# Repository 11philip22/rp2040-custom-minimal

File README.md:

# RP2040 Minimal Project for KiCad

**RP2040 Minimal** is a circuit design based on Raspberry Pi's **RP2040** microcontroller, provided as a **KiCad** project. This repository contains the `RP2040_minimal-edit_V3` revision by [Gerald](https://community.element14.com/members/geralds), which retains the original PCB outline and GPIO connectors while updating the layout, component sizes, and USB interface.

| Front | Back |
| :---: | :---: |
|  |  |

## Design Overview

1. Uses a **USB Type-C** connector in place of the original Micro USB connector.
2. Uses `0603` components in place of `0402` parts for easier assembly.
3. Improves the PCB layout while retaining the original board outline and **GPIO connectors**.
4. Includes improved **ESD protection** at the USB interface.
5. Includes project-local **symbols**, **footprints**, and **3D models** for editing the design in KiCad.

## Notes

- Open [`minimal-edit_V3.kicad_pro`](./minimal-edit_V3.kicad_pro) in **KiCad** to work with the schematic and PCB layout.
- Keep the bundled library directories alongside the project; the symbol and footprint tables use project-relative paths.

## Technical Documentation

The repository includes the following design files and previews:

- [KiCad Schematic](./minimal-edit_V3.kicad_sch)
- [KiCad PCB Layout](./minimal-edit_V3.kicad_pcb)
- [Schematic Preview](./images/RP2040-minimal-Rev3_sch.png)

| Front PCB Layout | Back PCB Layout |
| :---: | :---: |
|  |  |

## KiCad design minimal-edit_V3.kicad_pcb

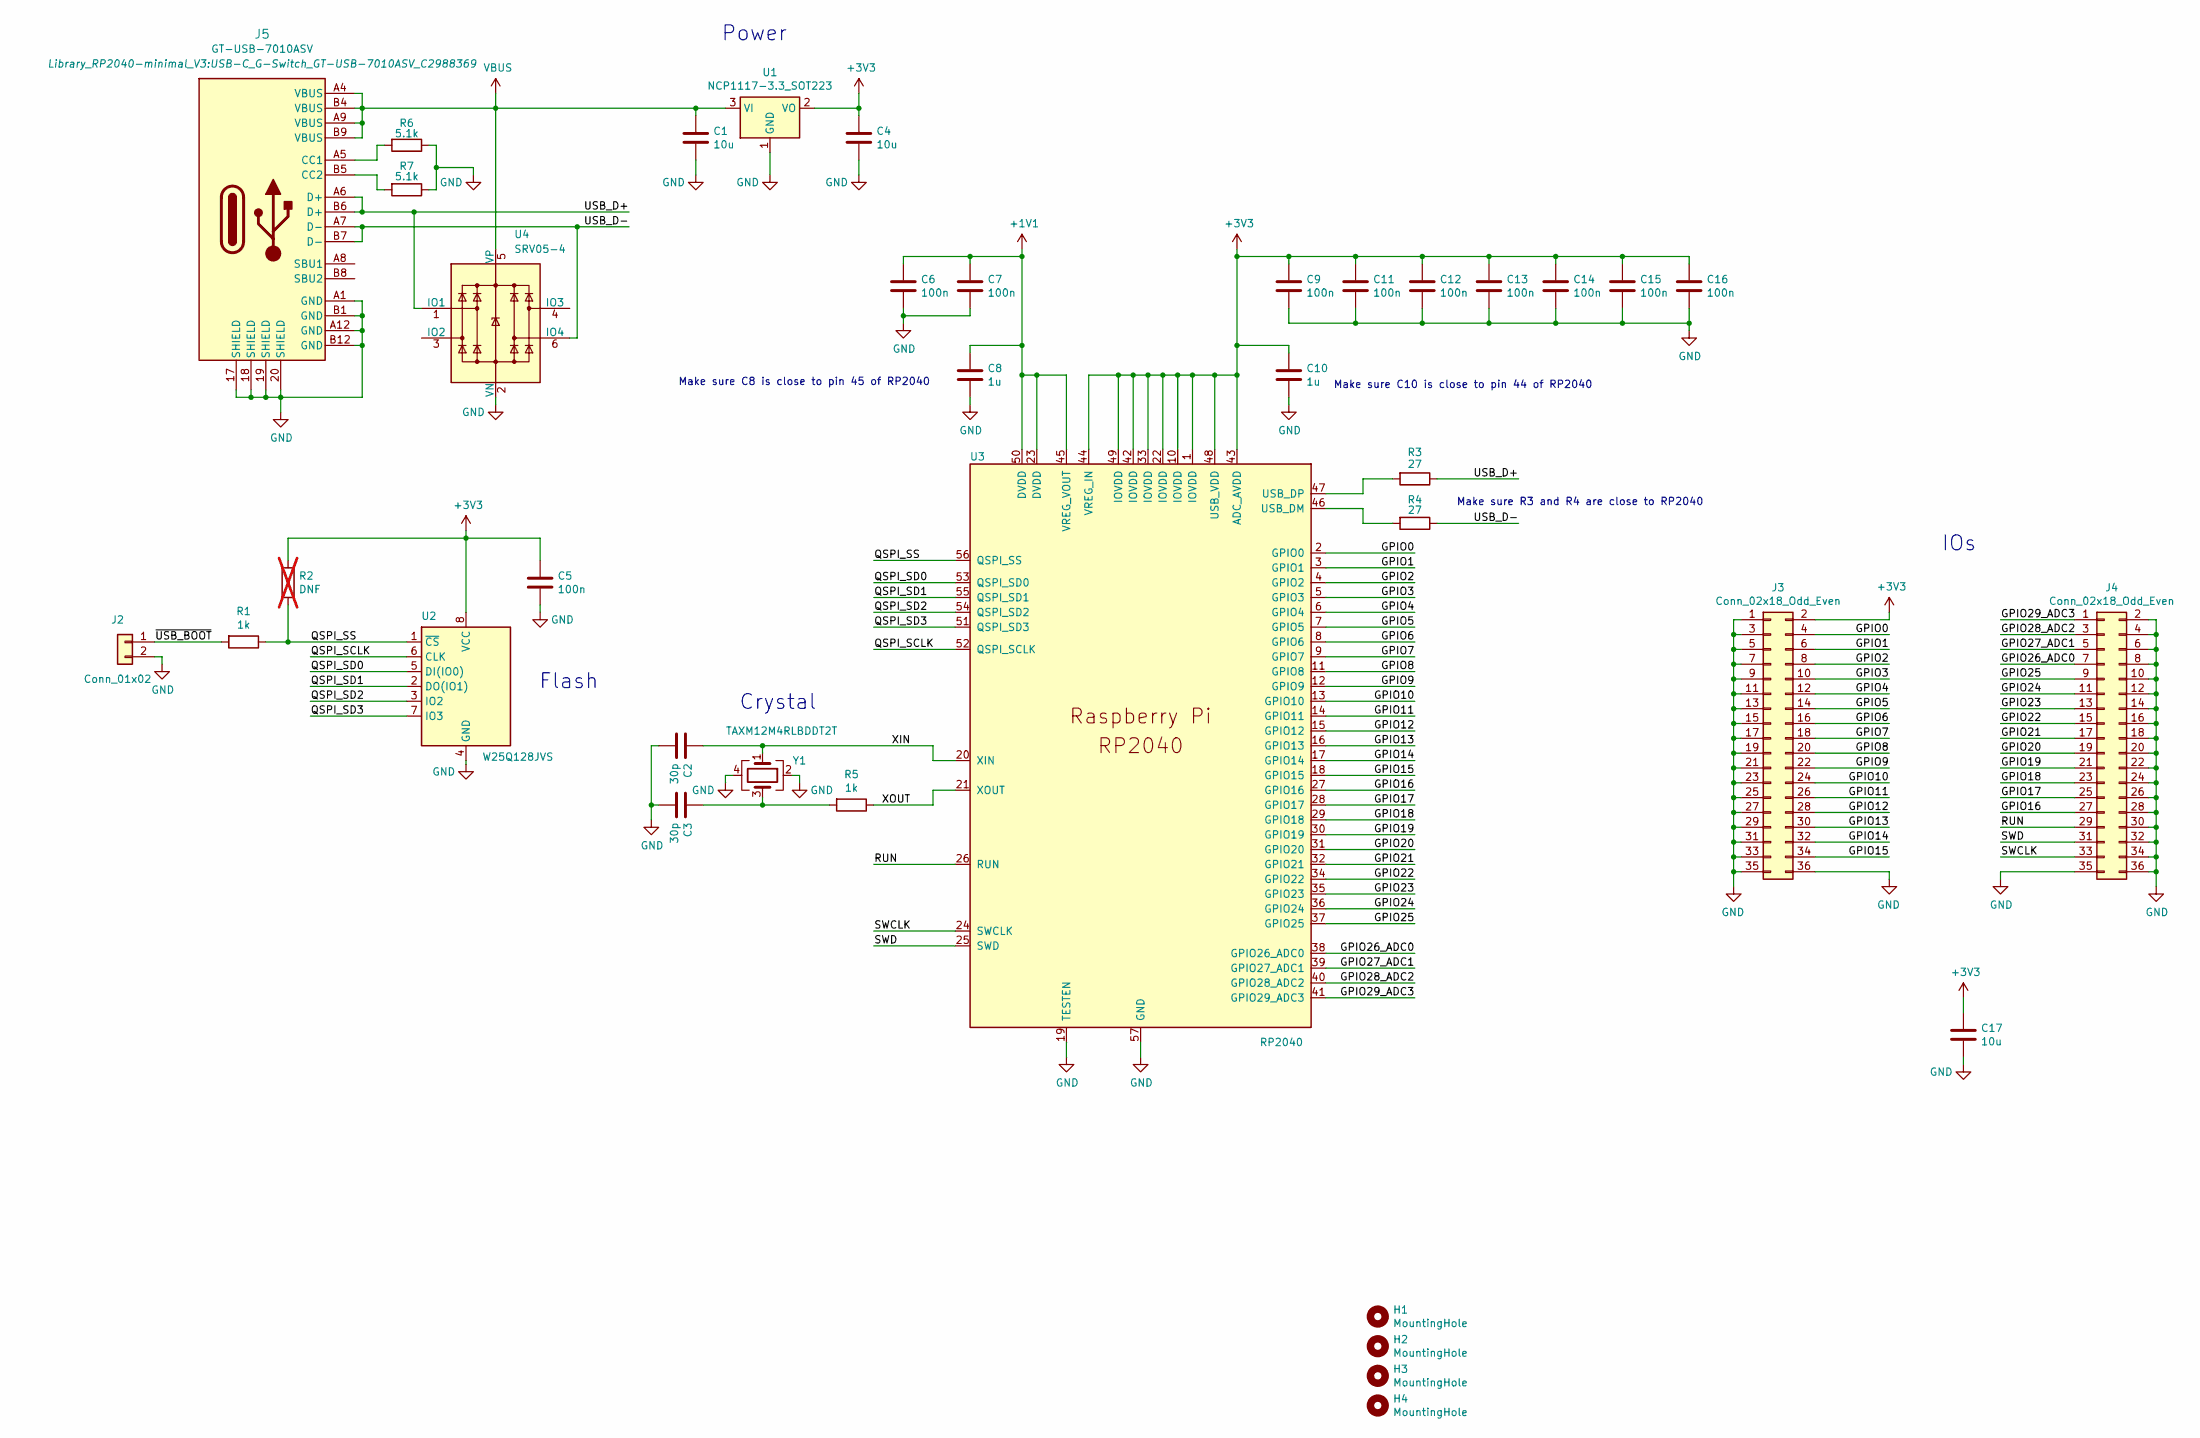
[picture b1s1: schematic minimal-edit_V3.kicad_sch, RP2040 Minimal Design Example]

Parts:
C1, C4, C17: 10u; C_1206_3216Metric; LCSC Part # C13585
C2, C3: 30p; C_0603_1608Metric; LCSC Part # C1658
C5, C6, C7, C9, C11, C12, C13, C14, C15, C16: 100n; C_0603_1608Metric; LCSC Part # C14663
C8, C10: 1u; C_0805_2012Metric; LCSC Part # C28323
H1, H2, H3, H4: MountingHole; MountingHole_2.7mm_M2.5
J2: Conn_01x02; PinHeader_1x02_P2.54mm_Vertical
J3, J4: Conn_02x18_Odd_Even; PinHeader_2x18_P2.54mm_Vertical
J5: GT-USB-7010ASV; USB-C_G-Switch_GT-USB-7010ASV_C2988369; LCSC Part # C2988369
R1, R5: 1k; R_0603_1608Metric; LCSC Part # C21190
R2: DNF; R_0603_1608Metric; not fitted
R3, R4: 27; R_0603_1608Metric; LCSC Part # C25190
R6, R7: 5.1k; R_0603_1608Metric; LCSC Part # C23186
U1: NCP1117-3.3_SOT223; SOT-223-3_TabPin2; LCSC Part # C26537
U2: W25Q128JVS; SOIC-8_5.3x5.3mm_P1.27mm; LCSC Part # C97521
U3: RP2040; QFN-56-1EP_7x7mm_P0.4mm_EP3.2x3.2mm_ThermalVias; LCSC Part # C2040
U4: SRV05-4; SOT-23-6; LCSC Part # C2836319
Y1: TAXM12M4RLBDDT2T; Crystal_SMD_3225-4Pin_3.2x2.5mm; LCSC Part # C133334

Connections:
+1V1: C6.1, C7.1, C8.1, U3.23 (DVDD), U3.45 (VREG_VOUT), U3.50 (DVDD)
+3V3: C4.1, C5.1, C9.1, C10.1, C11.1, C12.1, C13.1, C14.1, C15.1, C16.1, C17.1, J3.2, R2.1, U1.2 (VO), U2.8 (VCC), U3.1 (IOVDD), U3.10 (IOVDD), U3.22 (IOVDD), U3.33 (IOVDD), U3.42 (IOVDD), U3.43 (ADC_AVDD), U3.44 (VREG_IN), U3.48 (USB_VDD), U3.49 (IOVDD)
/GPIO0: J3.4, U3.2 (GPIO0)
/GPIO1: J3.6, U3.3 (GPIO1)
/GPIO2: J3.8, U3.4 (GPIO2)
/GPIO3: J3.10, U3.5 (GPIO3)
/GPIO4: J3.12, U3.6 (GPIO4)
/GPIO5: J3.14, U3.7 (GPIO5)
/GPIO6: J3.16, U3.8 (GPIO6)
/GPIO7: J3.18, U3.9 (GPIO7)
/GPIO8: J3.20, U3.11 (GPIO8)
/GPIO9: J3.22, U3.12 (GPIO9)
/GPIO10: J3.24, U3.13 (GPIO10)
/GPIO11: J3.26, U3.14 (GPIO11)
/GPIO12: J3.28, U3.15 (GPIO12)
/GPIO13: J3.30, U3.16 (GPIO13)
/GPIO14: J3.32, U3.17 (GPIO14)
/GPIO15: J3.34, U3.18 (GPIO15)
/GPIO16: J4.27, U3.27 (GPIO16)
/GPIO17: J4.25, U3.28 (GPIO17)
/GPIO18: J4.23, U3.29 (GPIO18)
/GPIO19: J4.21, U3.30 (GPIO19)
/GPIO20: J4.19, U3.31 (GPIO20)
/GPIO21: J4.17, U3.32 (GPIO21)
/GPIO22: J4.15, U3.34 (GPIO22)
/GPIO23: J4.13, U3.35 (GPIO23)
/GPIO24: J4.11, U3.36 (GPIO24)
/GPIO25: J4.9, U3.37 (GPIO25)
/GPIO26_ADC0: J4.7, U3.38 (GPIO26_ADC0)
/GPIO27_ADC1: J4.5, U3.39 (GPIO27_ADC1)
/GPIO28_ADC2: J4.3, U3.40 (GPIO28_ADC2)
/GPIO29_ADC3: J4.1, U3.41 (GPIO29_ADC3)
/QSPI_SCLK: U2.6 (CLK), U3.52 (QSPI_SCLK)
/QSPI_SD0: U2.5 (DI(IO0)), U3.53 (QSPI_SD0)
/QSPI_SD1: U2.2 (DO(IO1)), U3.55 (QSPI_SD1)
/QSPI_SD2: U2.3 (IO2), U3.54 (QSPI_SD2)
/QSPI_SD3: U2.7 (IO3), U3.51 (QSPI_SD3)
/QSPI_SS: R1.1, R2.2, U2.1 (~CS), U3.56 (QSPI_SS)
/RUN: J4.29, U3.26 (RUN)
/SWCLK: J4.33, U3.24 (SWCLK)
/SWD: J4.31, U3.25 (SWD)
/USB_D+: J5.A6 (D+), J5.B6 (D+), R3.1, U4.1 (IO1)
/USB_D-: J5.A7 (D-), J5.B7 (D-), R4.1, U4.6 (IO4)
/XIN: C2.1, U3.20 (XIN), Y1.1
/XOUT: R5.1, U3.21 (XOUT)
/~USB_BOOT: J2.1, R1.2
GND: C1.2, C2.2, C3.2, C4.2, C5.2, C6.2, C7.2, C8.2, C9.2, C10.2, C11.2, C12.2, C13.2, C14.2, C15.2, C16.2, C17.2, J2.2, J3.1, J3.3, J3.5, J3.7, J3.9, J3.11, J3.13, J3.15, J3.17, J3.19, J3.21, J3.23, J3.25, J3.27, J3.29, J3.31, J3.33, J3.35, J3.36, J4.2, J4.4, J4.6, J4.8, J4.10, J4.12, J4.14, J4.16, J4.18, J4.20, J4.22, J4.24, J4.26, J4.28, J4.30, J4.32, J4.34, J4.35, J4.36, J5.17 (SHIELD), J5.18 (SHIELD), J5.19 (SHIELD), J5.20 (SHIELD), J5.A1 (GND), J5.A12 (GND), J5.B1 (GND), J5.B12 (GND), R6.1, R7.1, U1.1 (GND), U2.4 (GND), U3.19 (TESTEN), U3.57 (GND), U4.2 (VN), Y1.2, Y1.4
unnamed: C3.1, R5.2, Y1.3
unnamed: J5.A5 (CC1), R6.2
unnamed: J5.B5 (CC2), R7.2
unnamed: R4.2, U3.46 (USB_DM)
unnamed: R3.2, U3.47 (USB_DP)
VBUS: C1.1, J5.A4 (VBUS), J5.A9 (VBUS), J5.B4 (VBUS), J5.B9 (VBUS), U1.3 (VI), U4.5 (VP)

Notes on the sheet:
IOs
Power
Crystal
Make sure C8 is close to pin 45 of RP2040
Make sure C10 is close to pin 44 of RP2040
Make sure R3 and R4 are close to RP2040
Flash

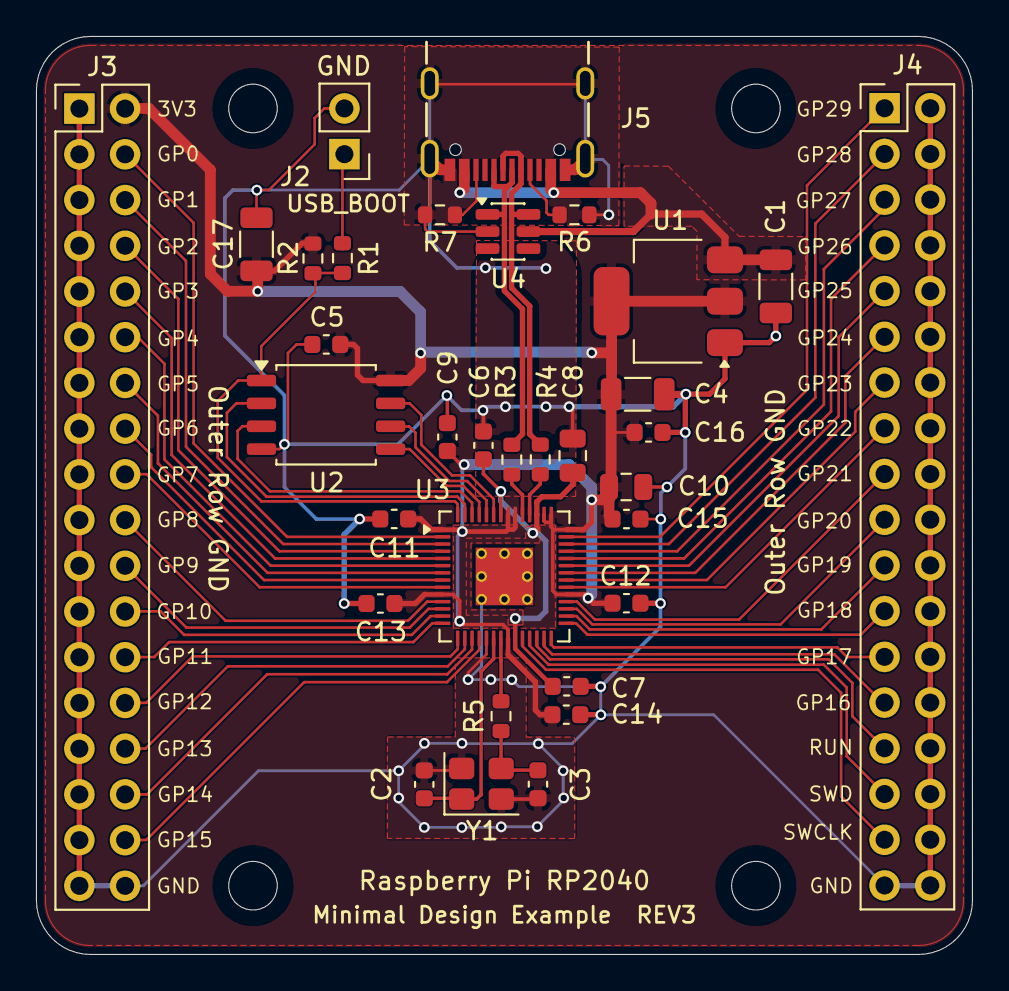
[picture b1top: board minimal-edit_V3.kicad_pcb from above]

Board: 2 copper layers, 52.0 x 51.0 mm, 37 parts (0 on the bottom side), 53 nets.

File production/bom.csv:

Designator,Footprint,Quantity,Value,LCSC Part #
"C1, C17, C4",1206,3,10u,C13585
"C10, C8",0805,2,1u,C28323
"C11, C12, C13, C14, C15, C16, C5, C6, C7, C9",0603,10,100n,C14663
"C2, C3",0603,2,15p,C1644
"H1, H2, H3, H4",MountingHole_2.7mm_M2.5,4,MountingHole,
J2,PinHeader_1x02_P2.54mm_Vertical,1,Conn_01x02,
"J3, J4",PinHeader_2x18_P2.54mm_Vertical,2,Conn_02x18_Odd_Even,
J5,CONN_USB4930-00-A_GCT,1,GT-USB-7010ASV,C2988369
"R1, R5",0603,2,1k,C21190
R2,0603,1,DNF,
"R3, R4",0603,2,27,C25190
"R6, R7",0603,2,5.1k,C23186
U1,SOT-223-3_TabPin2,1,NCP1117-3.3_SOT223,C26537
U2,SOIC-8_5.3x5.3mm_P1.27mm,1,W25Q128JVS,C97521
U3,QFN-56-1EP_7x7mm_P0.4mm_EP3.2x3.2mm_ThermalVias,1,RP2040,C2040
U4,SOT-23-6,1,SRV05-4,C2836319
Y1,Crystal_SMD_3225-4Pin_3.2x2.5mm,1,ABM8-272-T3,C20625731
